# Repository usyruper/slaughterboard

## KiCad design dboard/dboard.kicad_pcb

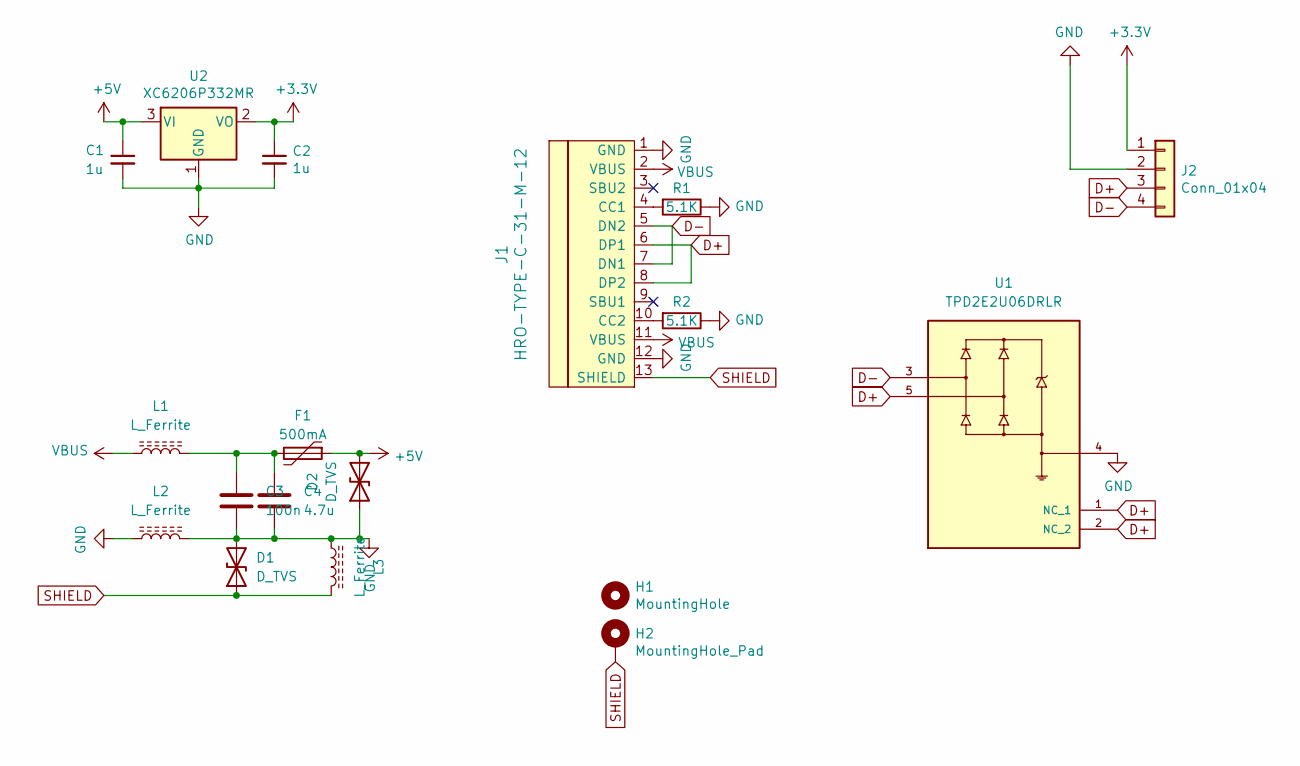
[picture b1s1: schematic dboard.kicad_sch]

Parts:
C1, C2: 1u; C_0402_1005Metric; LCSC C52923
C3: 100n; C_0402_1005Metric
C4: 4.7u; C_0402_1005Metric
D1: D_TVS; BSD3C051V
D2: D_TVS; D_SOD-123
F1: 500mA; Fuse_1206_3216Metric; jlc C70076
H1: MountingHole; M3_Via_Hole_NC
H2: MountingHole_Pad; M3_Via_Hole
J1: HRO-TYPE-C-31-M-12; HRO-TYPE-C-31-M-12-Assembly
J2: Conn_01x04; JST_SH_SM04B-SRSS-TB_1x04-1MP_P1.00mm_Horizontal
L1, L2, L3: L_Ferrite; BEADC1005X55N
R1, R2: 5.1K; R_0402_1005Metric; jlc C23186
U1: TPD2E2U06DRLR; SOTFL50P160X60-5N
U2: XC6206P332MR; SOT-23; LCSC C5446

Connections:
+3V3: C2.1, J2.1, U2.2 (VO)
+5V: C1.1, D2.2 (A2), F1.1, U2.3 (VI)
D+: J1.6 (DP1), J1.8 (DP2), J2.3, U1.1 (NC), U1.2 (NC), U1.5
D-: J1.5 (DN2), J1.7 (DN1), J2.4, U1.3
GND: C1.2, C2.2, C3.2, C4.2, D1.2 (A2), D2.1 (A1), J1.1 (GND), J1.12 (GND), J2.2, L2.1, L2.2, L3.1, R1.1, R2.1, U1.4, U2.1 (GND)
unnamed: C3.1, C4.1, F1.2, L1.2
unnamed: J1.4 (CC1), R1.2
unnamed: J1.10 (CC2), R2.2
SHIELD: D1.1 (A1), H2.1, J1.13 (SHIELD), L3.2
VBUS: J1.2 (VBUS), J1.11 (VBUS), L1.1

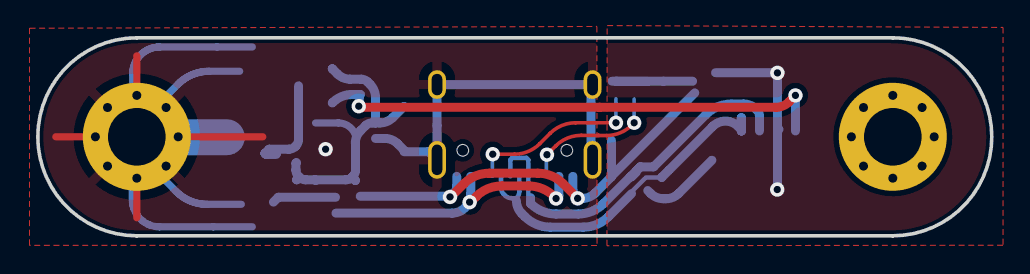
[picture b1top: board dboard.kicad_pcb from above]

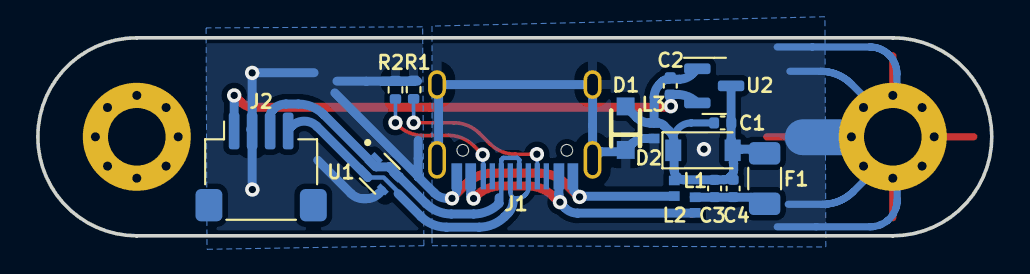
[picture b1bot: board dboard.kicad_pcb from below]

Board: 2 copper layers, 53.0 x 11.0 mm, 18 parts (16 on the bottom side), 10 nets.

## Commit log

2021-02-16 first
2021-02-16 remove
2021-02-16 expanded outline
    symmetrical around origin
2021-02-16 added tvs
2021-02-16 license
2021-02-16 rearranged
2021-02-21 curvy
